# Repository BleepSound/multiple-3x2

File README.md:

# multiple-3x2

Basic passive multiple, with a total of 3 inputs.

Each input is routed to 2 outputs.

All the sections "cascade" onto one another, so if you plug only input 1, you'll get that signal on all the 6 ouputs

You'll find the schematic of this module below: 

:warning: Fisrt place all the jack sockets, put in place the front panel, then fasten all jacks to it. Once this is done, you can solder them. 

[See bom globale](documentation/bom/Multiple-3x2_V1.0--iBoM.html)

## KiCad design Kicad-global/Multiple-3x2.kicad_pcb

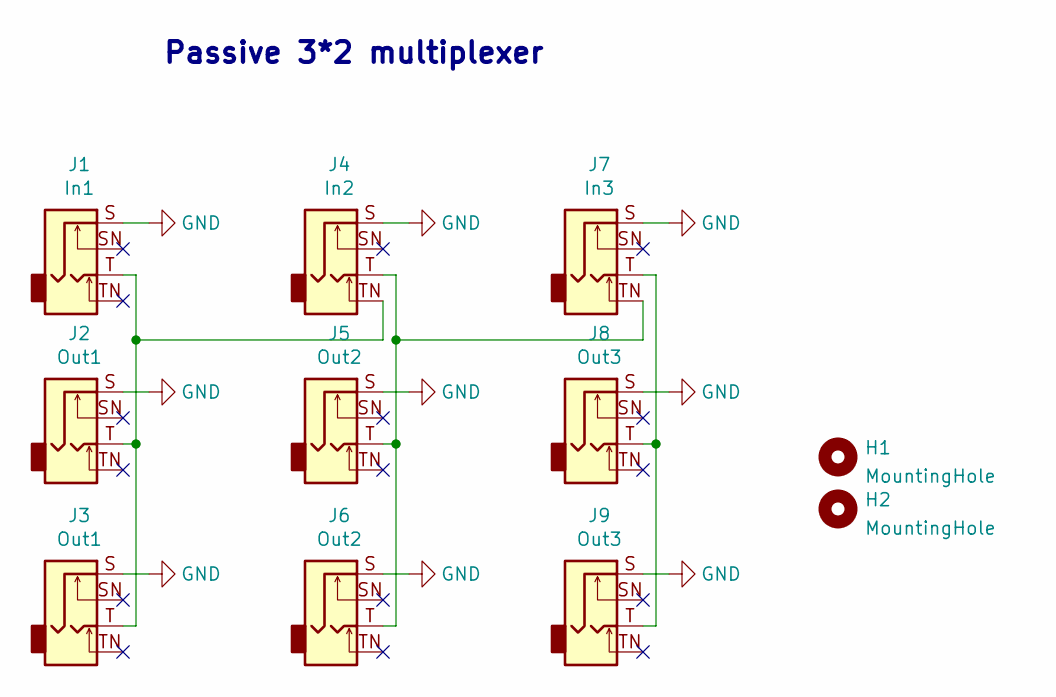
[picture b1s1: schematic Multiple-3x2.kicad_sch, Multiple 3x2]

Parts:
H1, H2: MountingHole; Doepfer Mounting hole
J1: In1; Thonkiconn
J2, J3: Out1; Thonkiconn
J4: In2; Thonkiconn
J5, J6: Out2; Thonkiconn
J7: In3; Thonkiconn
J8, J9: Out3; Thonkiconn

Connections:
GND: J1.S, J2.S, J3.S, J4.S, J5.S, J6.S, J7.S, J8.S, J9.S
unnamed: J1.T, J2.T, J3.T, J4.TN
unnamed: J4.T, J5.T, J6.T, J7.TN
unnamed: J7.T, J8.T, J9.T

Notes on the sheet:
Passive 3*2 multiplexer

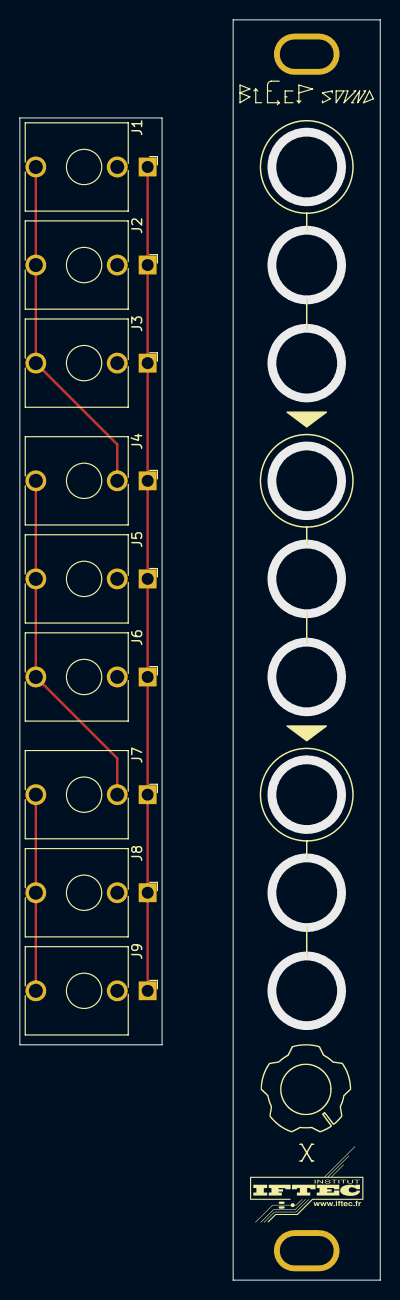
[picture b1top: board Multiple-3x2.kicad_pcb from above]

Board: 2 copper layers, 36.8 x 128.5 mm, 11 parts (0 on the bottom side), 4 nets.

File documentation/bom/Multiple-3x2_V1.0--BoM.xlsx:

Multiple-3x2_V1.0 Bill of Materials
Schematic: | Multiple-3x2 | Component Groups: | 1
Variant: | default | Component Count: | 9 (0 SMD/ 9 THT)
Revision: | 1.0 | Fitted Components: | 9 (0 SMD/ 9 THT)
Date: | 2023-09-23 | Number of PCBs: | 1
KiCad Version: | 7.0.7-7.0.7~ubuntu22.04.1 | Total Components: | 9
Row | Description | References | Value | Footprint | Quantity Per PCB | Comments
1 | Audio Jack, 2 Poles (Mono / TS), Switched Pole (Normalling) | J1 J2 J3 J4 J5 J6 J7 J8 J9 | In1 | Thonkiconn | 9 | Thonkiconn jack

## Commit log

2023-09-23 add all files and new repo organisation
2023-09-23 update kibot script
